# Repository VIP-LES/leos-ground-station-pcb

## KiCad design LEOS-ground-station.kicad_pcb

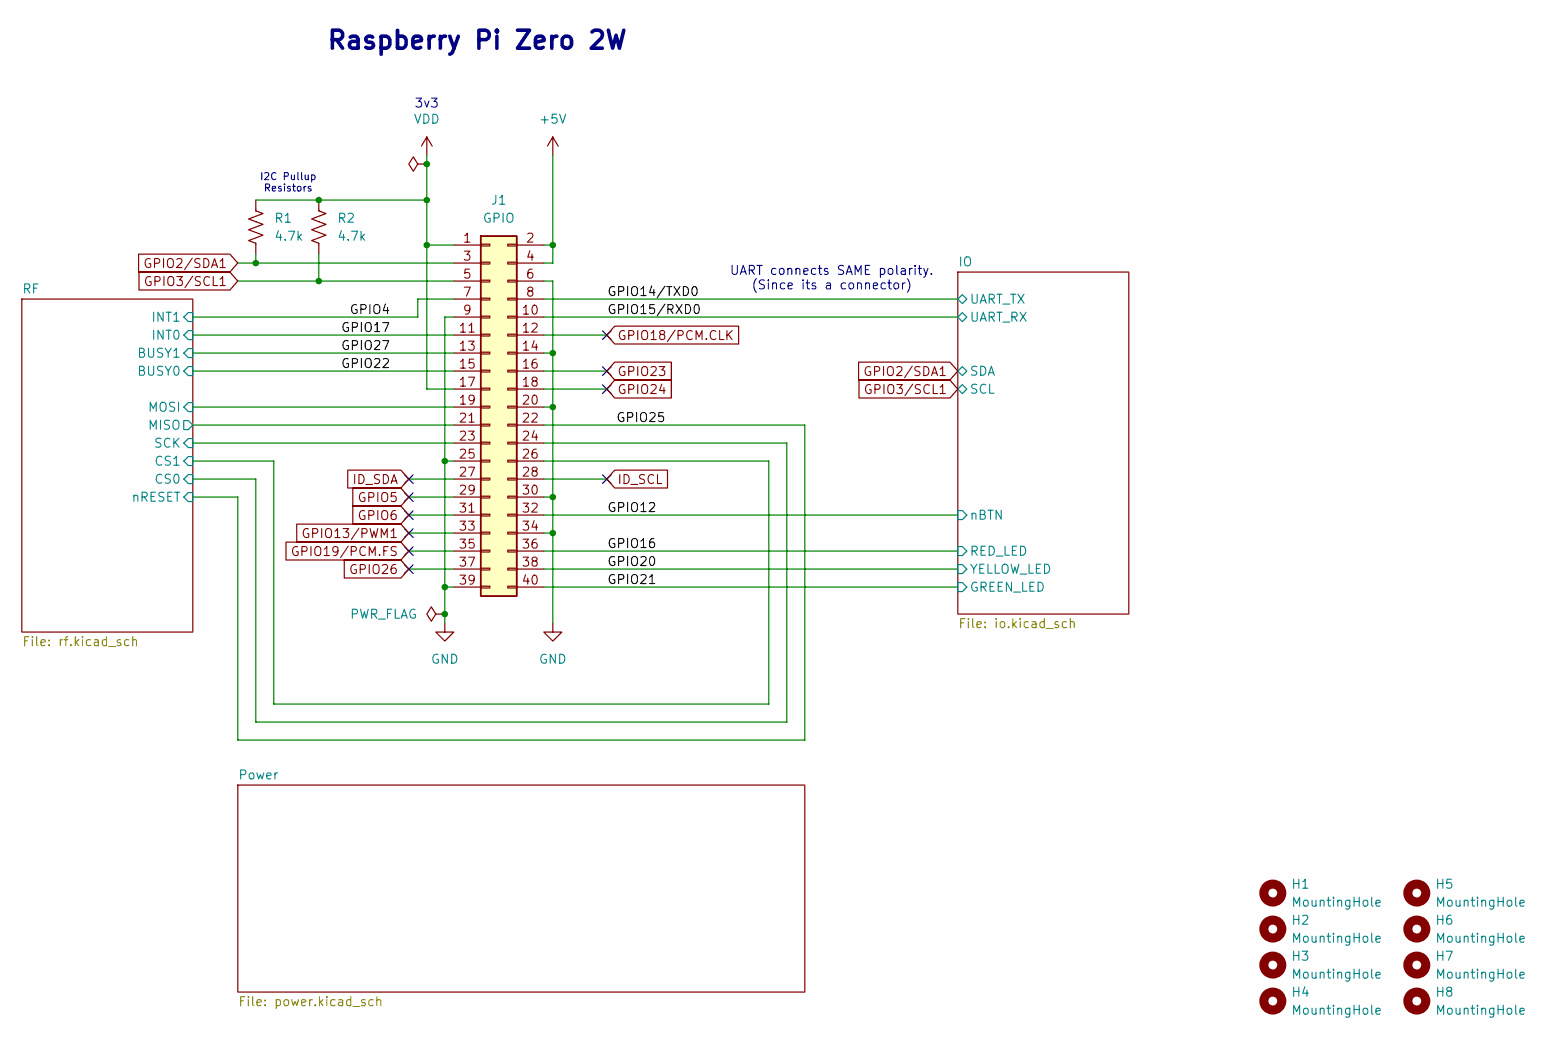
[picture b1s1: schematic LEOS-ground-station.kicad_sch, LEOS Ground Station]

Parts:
H1, H2, H3, H4: MountingHole; MountingHole_2.7mm_M2.5
H5, H6, H7, H8: MountingHole; MountingHole_3.2mm_M3
J1: GPIO; PinSocket_2x20_P2.54mm_Vertical
R1, R2: 4.7k; R_0805_2012Metric; MPN CRCW08054K70FKEA; Digikey 541-4.70KCCT-ND

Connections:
+5V: J1.2, J1.4; also elsewhere on the board
/GPIO4: J1.7; also elsewhere on the board
/GPIO12: J1.32; also elsewhere on the board
/GPIO14/TXD0: J1.8; also elsewhere on the board
/GPIO15/RXD0: J1.10; also elsewhere on the board
/GPIO16: J1.36; also elsewhere on the board
/GPIO17: J1.11; also elsewhere on the board
/GPIO20: J1.38; also elsewhere on the board
/GPIO21: J1.40; also elsewhere on the board
/GPIO22: J1.15; also elsewhere on the board
/GPIO25: J1.22; also elsewhere on the board
/GPIO27: J1.13; also elsewhere on the board
/RF/CS0: J1.24; also elsewhere on the board
/RF/CS1: J1.26; also elsewhere on the board
/RF/MISO: J1.21; also elsewhere on the board
/RF/MOSI: J1.19; also elsewhere on the board
/RF/SCK: J1.23; also elsewhere on the board
GND: J1.6, J1.9, J1.14, J1.20, J1.25, J1.30, J1.34, J1.39; also elsewhere on the board
GPIO2/SDA1: J1.3, R1.2; also elsewhere on the board
GPIO3/SCL1: J1.5, R2.2; also elsewhere on the board
GPIO5: J1.29
GPIO6: J1.31
GPIO13/PWM1: J1.33
GPIO18/PCM.CLK: J1.12
GPIO19/PCM.FS: J1.35
GPIO23: J1.16
GPIO24: J1.18
GPIO26: J1.37
ID_SCL: J1.28
ID_SDA: J1.27
VDD: J1.1, J1.17, R1.1, R2.1; also elsewhere on the board

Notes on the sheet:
3v3
Raspberry Pi Zero 2W
I2C Pullup Resistors
UART connects SAME polarity. (Since its a connector)

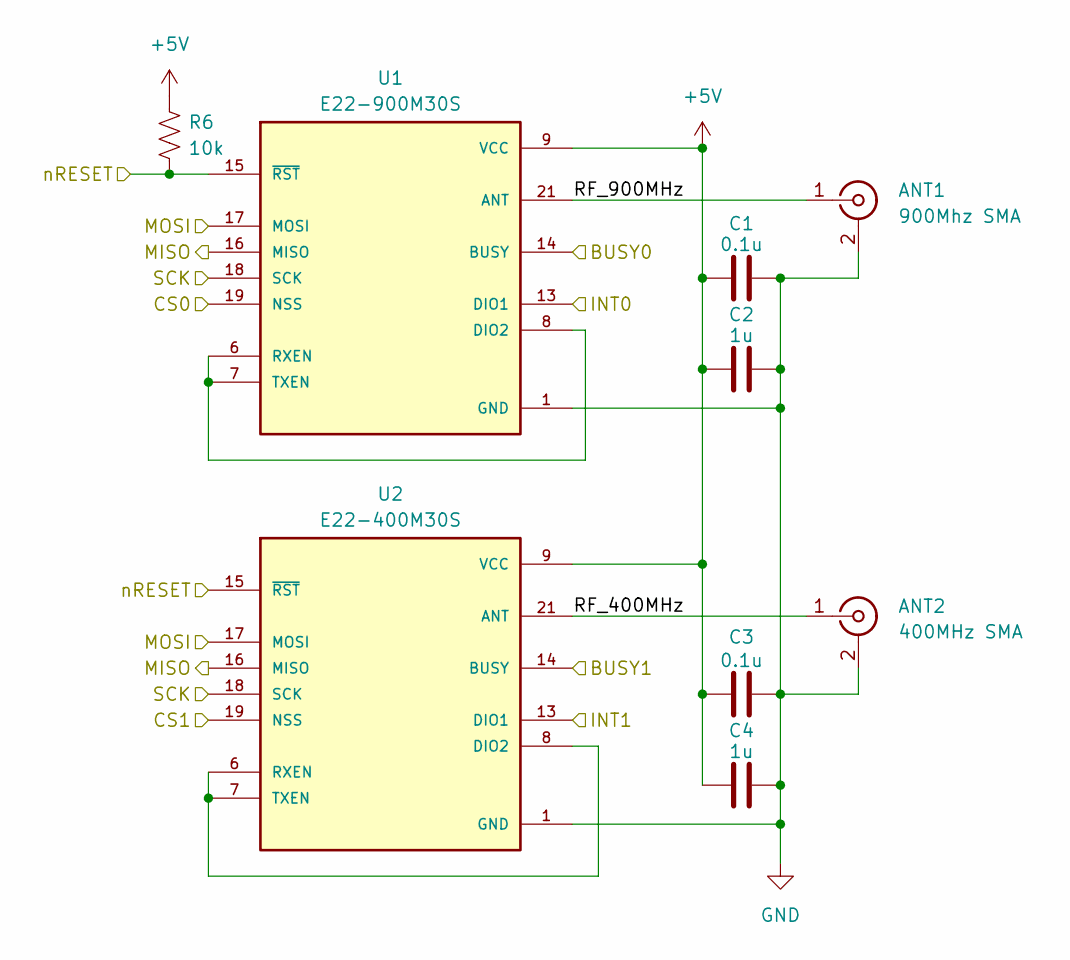
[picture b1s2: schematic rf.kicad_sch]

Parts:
ANT1: 900Mhz SMA; SMA_Molex_73251-1153_EdgeMount_Horizontal; MPN 0732511153; Digikey 900-0732511153-ND
ANT2: 400MHz SMA; SMA_Molex_73251-1153_EdgeMount_Horizontal; MPN 0732511153; Digikey 900-0732511153-ND
C1, C3: 0.1u; C_0603_1608Metric; MPN CL10B104KB8NNNL; Digikey 1276-CL10B104KB8NNNLCT-ND
C2, C4: 1u; C_0603_1608Metric; MPN CL10B105KA8NNNC; Digikey 1276-1184-1-ND
R6: 10k; R_0805_2012Metric; MPN CRCW080510K0FKEA; Digikey 541-10.0KCCT-ND
U1: E22-900M30S; XCVR_E22-900M30S; MPN E22-900M30S
U2: E22-400M30S; XCVR_E22-900M30S; MPN E22-400M30S

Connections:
+5V: C1.1, C2.1, C3.1, C4.1, R6.1, U1.9 (VCC), U1.10 (VCC), U2.9 (VCC), U2.10 (VCC); also elsewhere on the board
/GPIO4: U2.13 (DIO1); also elsewhere on the board
/GPIO17: U1.13 (DIO1); also elsewhere on the board
/GPIO22: U1.14 (BUSY); also elsewhere on the board
/GPIO25: R6.2, U1.15 (~RST), U2.15 (~RST); also elsewhere on the board
/GPIO27: U2.14 (BUSY); also elsewhere on the board
/RF/CS0: U1.19 (NSS); also elsewhere on the board
/RF/CS1: U2.19 (NSS); also elsewhere on the board
/RF/MISO: U1.16 (MISO), U2.16 (MISO); also elsewhere on the board
/RF/MOSI: U1.17 (MOSI), U2.17 (MOSI); also elsewhere on the board
/RF/RF_400MHz: ANT2.1 (In), U2.21 (ANT)
/RF/RF_900MHz: ANT1.1 (In), U1.21 (ANT)
/RF/SCK: U1.18 (SCK), U2.18 (SCK); also elsewhere on the board
GND: ANT1.2 (Ext), ANT2.2 (Ext), C1.2, C2.2, C3.2, C4.2, U1.1 (GND), U1.2 (GND), U1.3 (GND), U1.4 (GND), U1.5 (GND), U1.11 (GND), U1.12 (GND), U1.20 (GND), U1.22 (GND), U2.1 (GND), U2.2 (GND), U2.3 (GND), U2.4 (GND), U2.5 (GND), U2.11 (GND), U2.12 (GND), U2.20 (GND), U2.22 (GND); also elsewhere on the board
unnamed: U1.6 (RXEN), U1.7 (TXEN), U1.8 (DIO2)
unnamed: U2.6 (RXEN), U2.7 (TXEN), U2.8 (DIO2)

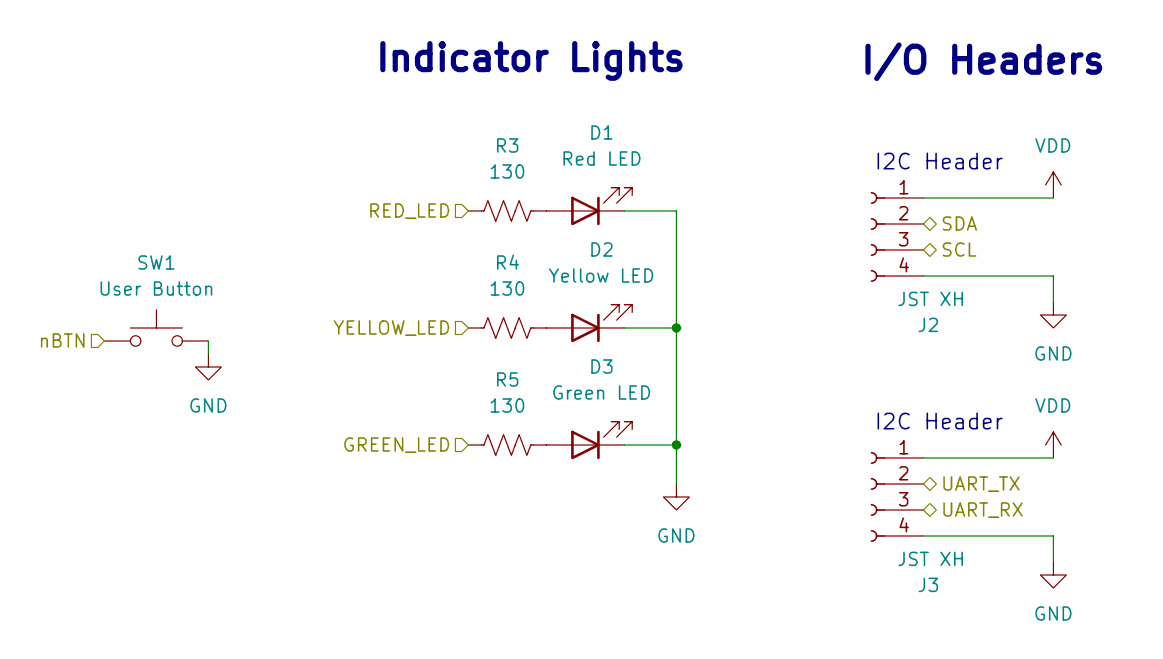
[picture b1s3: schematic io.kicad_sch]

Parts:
D1: Red LED; LED_1206_3216Metric; MPN LTST-C150KRKT; Digikey 160-1405-1-ND
D2: Yellow LED; LED_1206_3216Metric; MPN LTST-C150KSKT; Digikey 160-1406-1-ND
D3: Green LED; LED_1206_3216Metric; MPN LTST-C230KGKT; Digikey 160-1456-1-ND
J2, J3: JST XH; JST_XH_S4B-XH-A_1x04_P2.50mm_Horizontal; MPN S4B-XH-A; Digikey 455-2243-ND
R3, R4, R5: 130; R_0805_2012Metric; MPN CRCW0805130RFKEA; Digikey 541-130CCT-ND
SW1: User Button; SW_PUSH_6mm; MPN PTS645SK50-2 LFS; Digikey CKN9082-ND

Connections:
/GPIO12: SW1.1; also elsewhere on the board
/GPIO14/TXD0: J3.2; also elsewhere on the board
/GPIO15/RXD0: J3.3; also elsewhere on the board
/GPIO16: R3.1; also elsewhere on the board
/GPIO20: R4.1; also elsewhere on the board
/GPIO21: R5.1; also elsewhere on the board
GND: D1.1 (K), D2.1 (K), D3.1 (K), J2.4, J3.4, SW1.2; also elsewhere on the board
GPIO2/SDA1: J2.2; also elsewhere on the board
GPIO3/SCL1: J2.3; also elsewhere on the board
unnamed: D1.2 (A), R3.2
unnamed: D2.2 (A), R4.2
unnamed: D3.2 (A), R5.2
VDD: J2.1, J3.1; also elsewhere on the board

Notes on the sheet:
I2C Header
I/O Headers
Indicator Lights

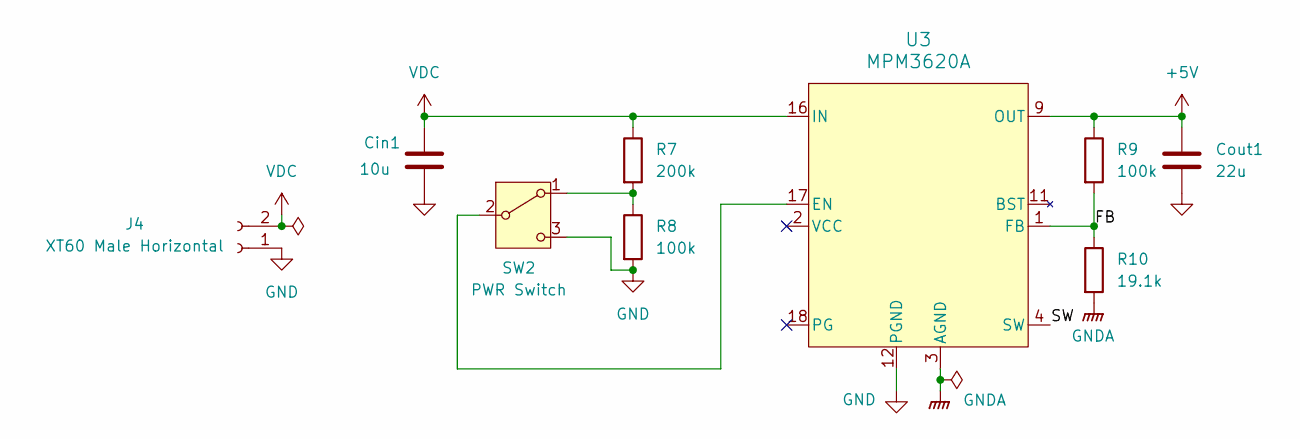
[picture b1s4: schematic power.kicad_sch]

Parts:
Cin1: 10u; C_0805_2012Metric; MPN CL21B106KOQNNNE; Digikey 1276-2872-1-ND
Cout1: 22u; C_0805_2012Metric; MPN CL21A226MAYNNNE; Digikey 1276-CL21A226MAYNNNECT-ND
J4: XT60 Male Horizontal; AMASS_XT60IPW-M_1x03_P7.20mm_Horizontal
R7: 200k; R_0805_2012Metric; MPN CRCW0805200KFKEA; Digikey 541-200KCCT-ND
R8, R9: 100k; R_0805_2012Metric; MPN CRCW0805100KFKEA; Digikey 541-100KCCT-ND
R10: 19.1k; R_0805_2012Metric; MPN CRCW080519K1FKEA; Digikey 541-19.1KCCT-ND
SW2: PWR Switch; SW_Slide_SPDT_Angled_CK_OS102011MA1Q; MPN OS102011MA1QN1; Digikey CKN9559-ND
U3: MPM3620A; IC18_MPM3620AGQV-Z_MNP; MPN MPM3620AGQV-Z; Digikey 1589-1764-1-ND

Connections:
+5V: Cout1.1, R9.1, U3.7 (OUT), U3.8 (OUT), U3.9 (OUT), U3.22 (OUT); also elsewhere on the board
/Power/FB: R9.2, R10.1, U3.1 (FB)
/Power/SW: U3.4 (SW), U3.5 (SW), U3.6 (SW), U3.21 (SW)
GND: Cin1.2, Cout1.2, J4.1, R8.2, SW2.3 (C), U3.12 (PGND), U3.13 (PGND), U3.14 (PGND); also elsewhere on the board
GNDA: R10.2, U3.3 (AGND)
unnamed: R7.2, R8.1, SW2.1 (A)
unnamed: SW2.2 (B), U3.17 (EN)
VDC: Cin1.1, J4.2, R7.1, U3.16 (IN)

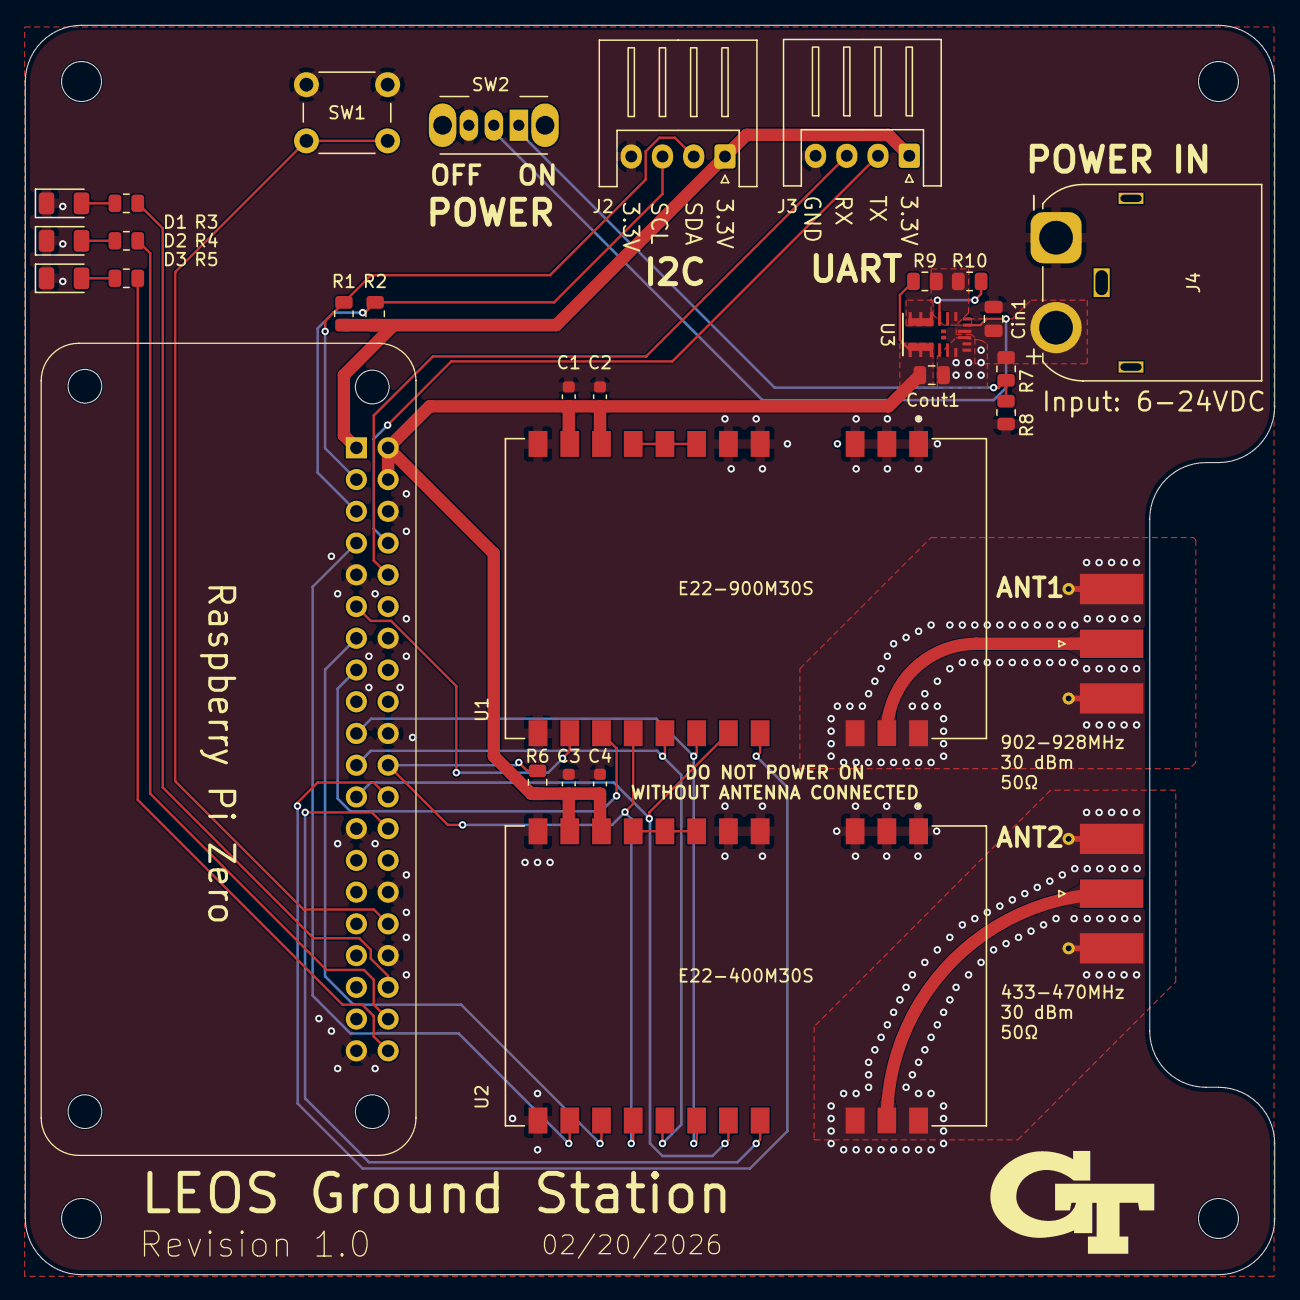
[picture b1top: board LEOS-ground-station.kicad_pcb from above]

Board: 2 copper layers, 100.0 x 100.0 mm, 38 parts (1 on the bottom side), 34 nets.

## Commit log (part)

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2026-02-20 v1.0 Ground Station with buck power, rpi0, and dual LoRa
